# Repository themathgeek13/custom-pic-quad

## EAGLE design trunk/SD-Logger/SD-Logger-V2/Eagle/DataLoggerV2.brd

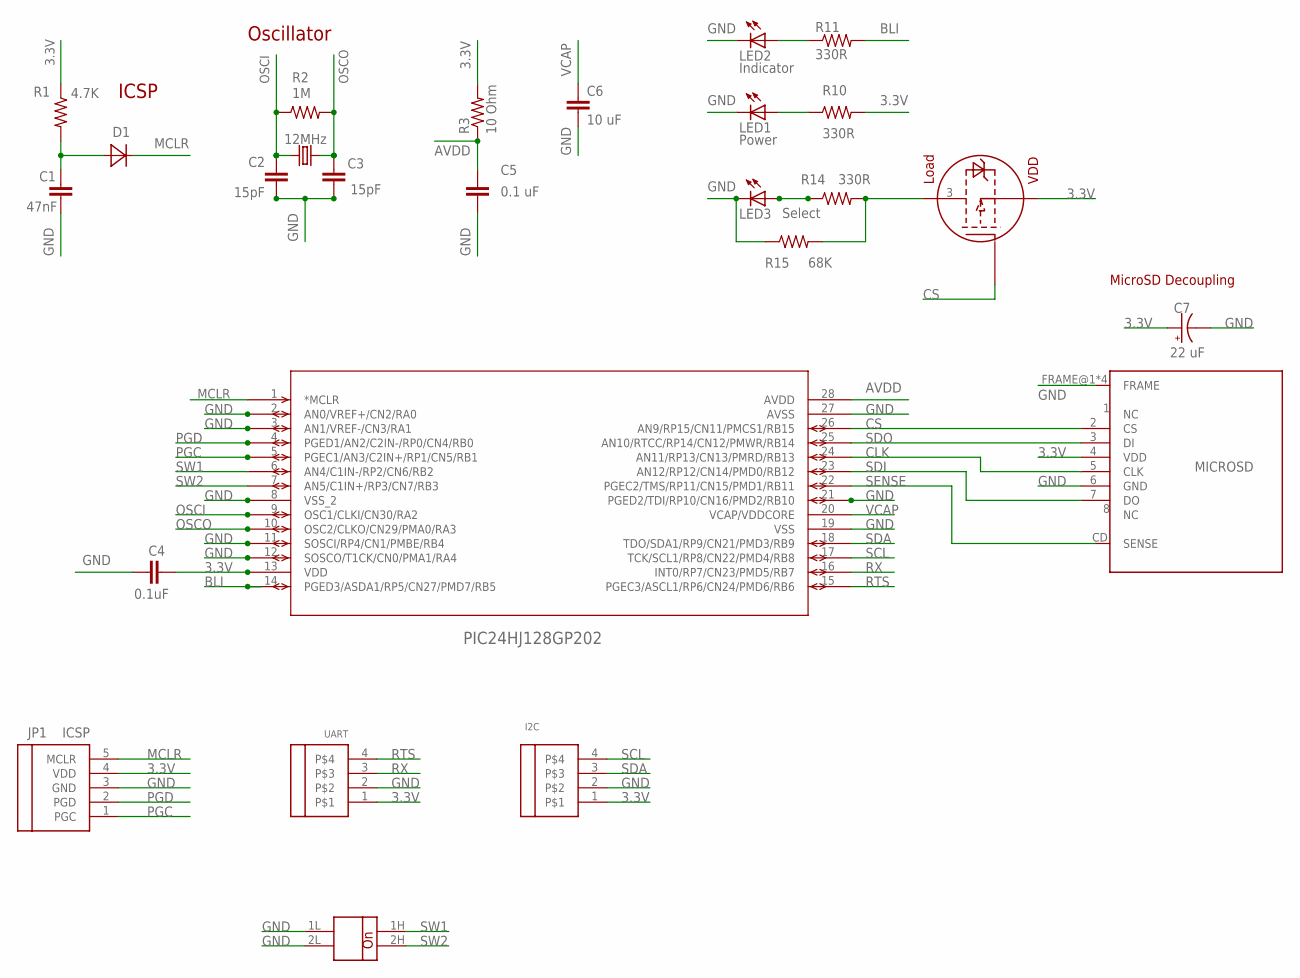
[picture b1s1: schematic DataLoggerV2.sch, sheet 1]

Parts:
C1: 47nF; 0805_INCH-HS-CAP
C2, C3: 15pF; 0805_INCH-HS-CAP
C4: 0.1uF; 0603_INCH-HS-CAP
C5: 0.1 uF; 0603_INCH-HS-CAP
C6: 10 uF; 1210_INCH-HS-CAP
C7: 22 uF; TANT-C-6032
D1: DIODE_1206; 1206_INCH-HS-DIODE
I2C: HEADER-04_JST-ZH_JST-ZH; 1X04-JST-ZH
JP1: ICSP; 1X05-JST-ZH
LED1: Power; 1206_INCH-HS-LED
LED2: Indicator; 1206_INCH-HS-LED
LED3: Select; 1206_INCH-HS-LED
P-FET: NTS2101P; SOT-323-0NSEMI
Q1: 12MHz; CRYSTAL-SMD-5.0X3.2
R1: 4.7K; 0805_INCH-HS
R2: 1M; 0805_INCH-HS
R3: 10 Ohm; 0805_INCH-HS
R10, R11, R14: 330R; 0805_INCH-HS
R15: 68K; 0805_INCH-HS
U$1: PIC24HJ128GP202; SOIC28-W_MC
U$2: MICROSD; MICROSD_V1
U$3: SWITCH-2_HALF-PITCH; DIP-2-HP
UART: HEADER-04_JST-ZH_JST-ZH; 1X04-JST-ZH

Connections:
3.3V: C4.1, C7.+, I2C.1, JP1.4 (VDD), P-FET.2 (S), R1.1, R3.2, R10.2, U$1.13 (VDD), U$2.4 (VDD), UART.1; also elsewhere on the board
AVDD: C5.1, R3.1, U$1.28 (AVDD)
BLI: R11.2, U$1.14 (PGED3/ASDA1/RP5/CN27/PMD7/RB5)
CLK: U$1.24 (AN11/RP13/CN13/PMRD/RB13), U$2.5 (CLK); also elsewhere on the board
CS: P-FET.1 (G), U$1.26 (AN9/RP15/CN11/PMCS1/RB15), U$2.2 (CS); also elsewhere on the board
GND: C1.2, C2.1, C3.1, C4.2, C5.2, C6.P$2 (2), C7.-, I2C.2, JP1.3 (GND), LED1.C, LED2.C, LED3.C, R15.1, U$1.2 (AN0/VREF+/CN2/RA0), U$1.3 (AN1/VREF-/CN3/RA1), U$1.8 (VSS_2), U$1.11 (SOSCI/RP4/CN1/PMBE/RB4), U$1.12 (SOSCO/T1CK/CN0/PMA1/RA4), U$1.19 (VSS), U$1.21 (PGED2/TDI/RP10/CN16/PMD2/RB10), U$1.27 (AVSS), U$2.6 (GND), U$2.FRAME@1 (FRAME), U$2.FRAME@2 (FRAME), U$2.FRAME@3 (FRAME), U$2.FRAME@4 (FRAME), U$3.1L, U$3.2L, UART.2; also elsewhere on the board
MCLR: D1.C, JP1.5 (MCLR), U$1.1 (*MCLR)
unnamed: C1.1, D1.A, R1.2
unnamed: LED3.A, R14.1
unnamed: LED1.A, R10.1
unnamed: LED2.A, R11.1
unnamed: P-FET.3 (D), R14.2, R15.2
OSCI: C2.2, Q1.P$2 (2), R2.1, U$1.9 (OSC1/CLKI/CN30/RA2)
OSCO: C3.2, Q1.P$1 (1), R2.2, U$1.10 (OSC2/CLKO/CN29/PMA0/RA3)
PGC: JP1.1 (PGC), U$1.5 (PGEC1/AN3/C2IN+/RP1/CN5/RB1)
PGD: JP1.2 (PGD), U$1.4 (PGED1/AN2/C2IN-/RP0/CN4/RB0)
RTS: U$1.15 (PGEC3/ASCL1/RP6/CN24/PMD6/RB6), UART.4; also elsewhere on the board
RX: U$1.16 (INT0/RP7/CN23/PMD5/RB7), UART.3; also elsewhere on the board
SCL: I2C.4, U$1.17 (TCK/SCL1/RP8/CN22/PMD4/RB8); also elsewhere on the board
SDA: I2C.3, U$1.18 (TDO/SDA1/RP9/CN21/PMD3/RB9); also elsewhere on the board
SDI: U$1.23 (AN12/RP12/CN14/PMD0/RB12), U$2.7 (DO); also elsewhere on the board
SDO: U$1.25 (AN10/RTCC/RP14/CN12/PMWR/RB14), U$2.3 (DI); also elsewhere on the board
SENSE: U$1.22 (PGEC2/TMS/RP11/CN15/PMD1/RB11), U$2.CD (SENSE)
SW1: U$1.6 (AN4/C1IN-/RP2/CN6/RB2), U$3.1H
SW2: U$1.7 (AN5/C1IN+/RP3/CN7/RB3), U$3.2H
VCAP: C6.P$1 (1), U$1.20 (VCAP/VDDCORE)

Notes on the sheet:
ICSP
Oscillator
MicroSD Decoupling

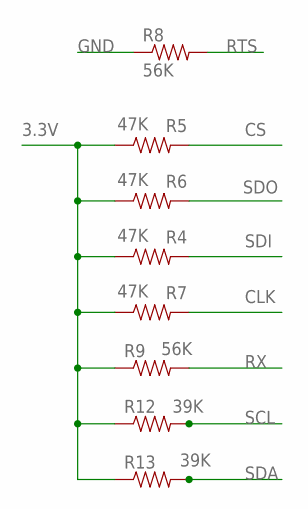
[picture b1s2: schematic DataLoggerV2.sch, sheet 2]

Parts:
R4, R5, R6, R7: 47K; 0805_INCH-HS
R8, R9: 56K; 0805_INCH-HS
R12, R13: 39K; 0805_INCH-HS

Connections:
3.3V: R4.1, R5.1, R6.1, R7.1, R9.1, R12.1, R13.1; also elsewhere on the board
CLK: R7.2; also elsewhere on the board
CS: R5.2; also elsewhere on the board
GND: R8.1; also elsewhere on the board
RTS: R8.2; also elsewhere on the board
RX: R9.2; also elsewhere on the board
SCL: R12.2; also elsewhere on the board
SDA: R13.2; also elsewhere on the board
SDI: R4.2; also elsewhere on the board
SDO: R6.2; also elsewhere on the board

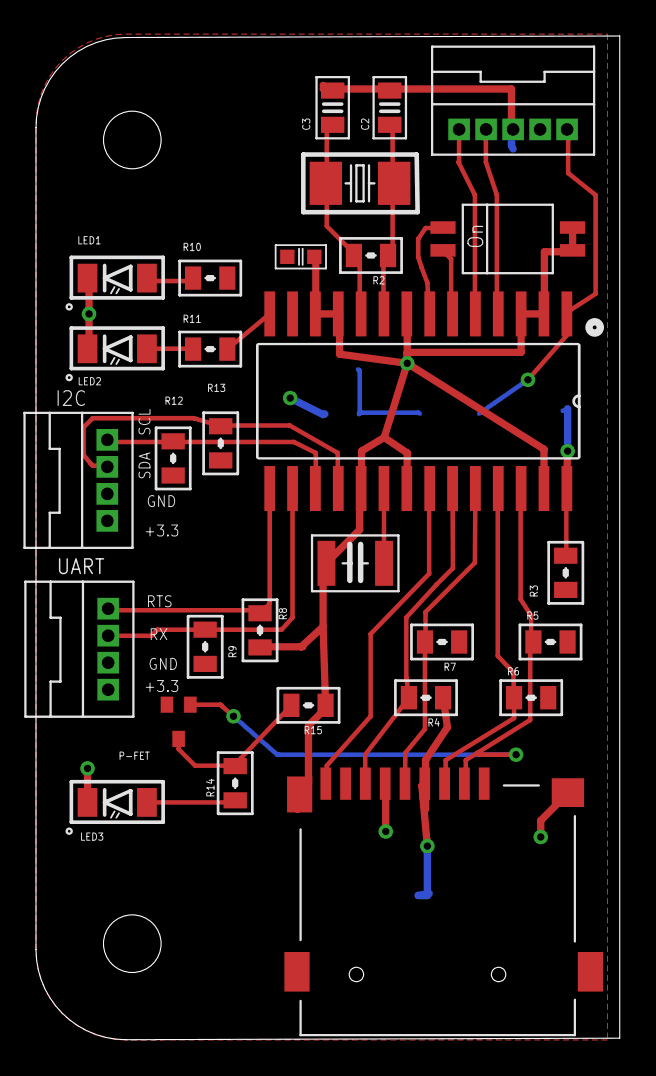
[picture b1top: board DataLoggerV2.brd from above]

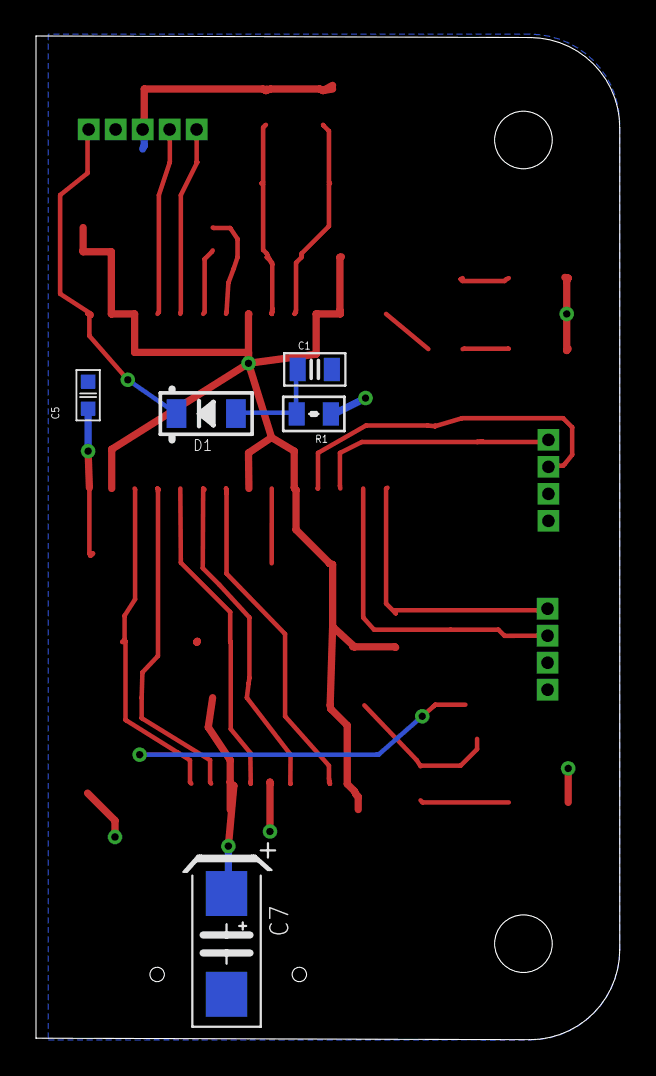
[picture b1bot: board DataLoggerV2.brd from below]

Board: 2 copper layers, 32.4 x 55.8 mm, 34 parts (5 on the bottom side), 26 nets.

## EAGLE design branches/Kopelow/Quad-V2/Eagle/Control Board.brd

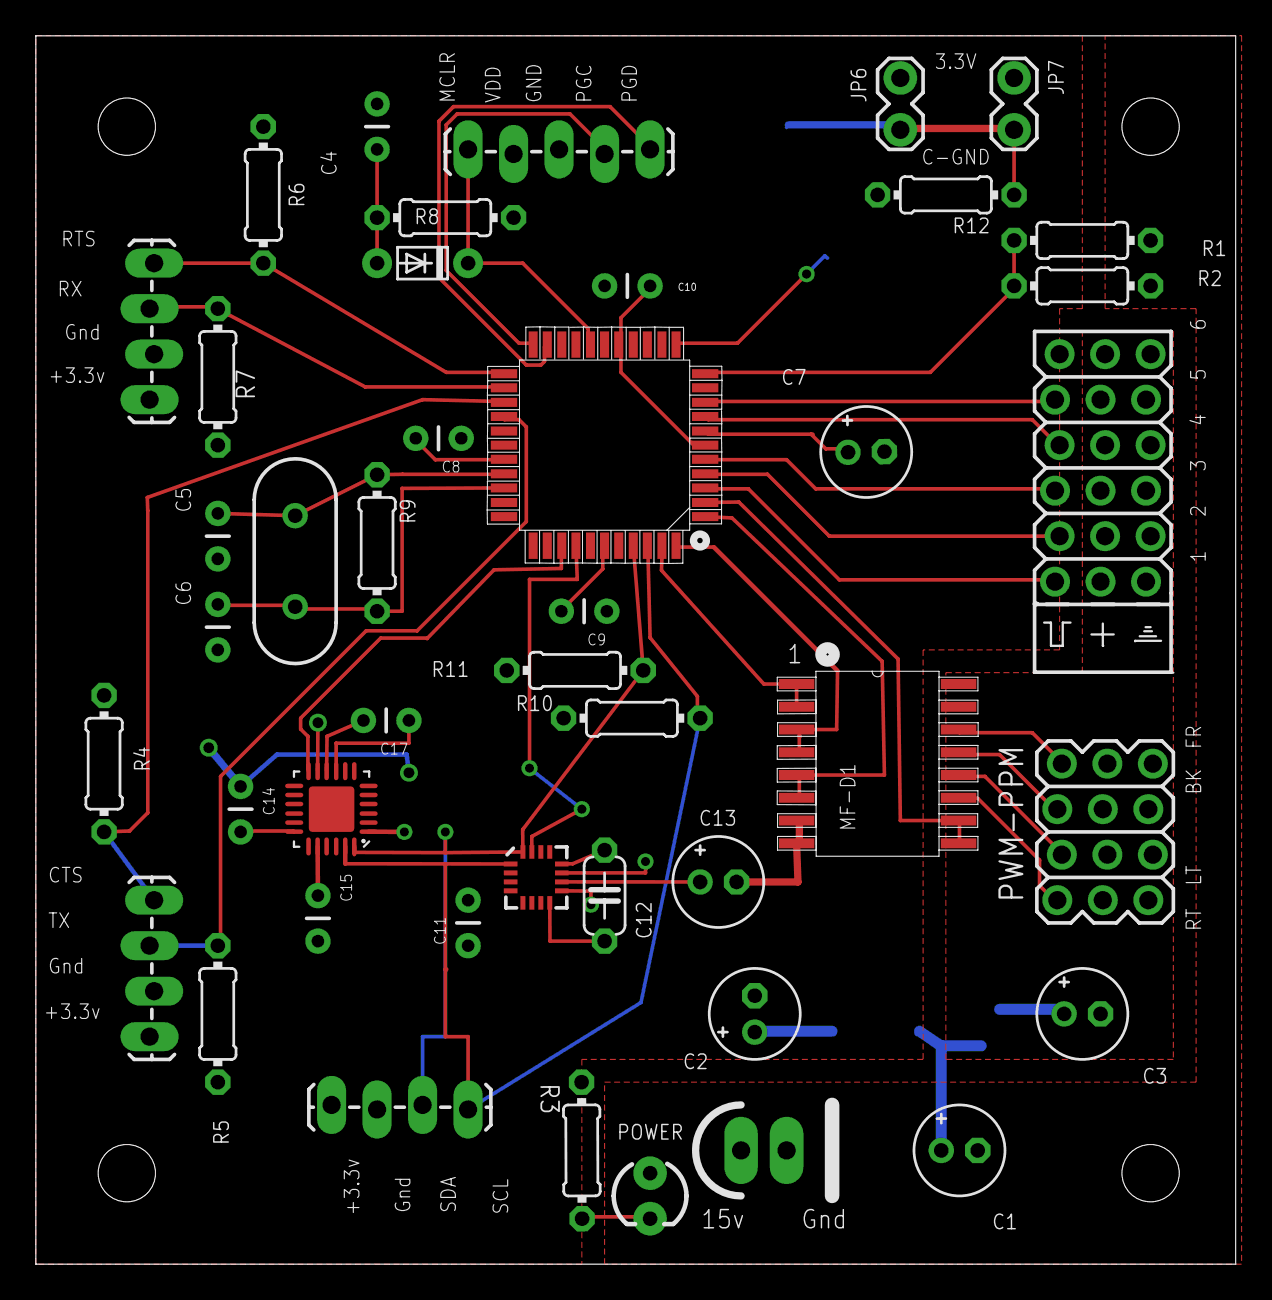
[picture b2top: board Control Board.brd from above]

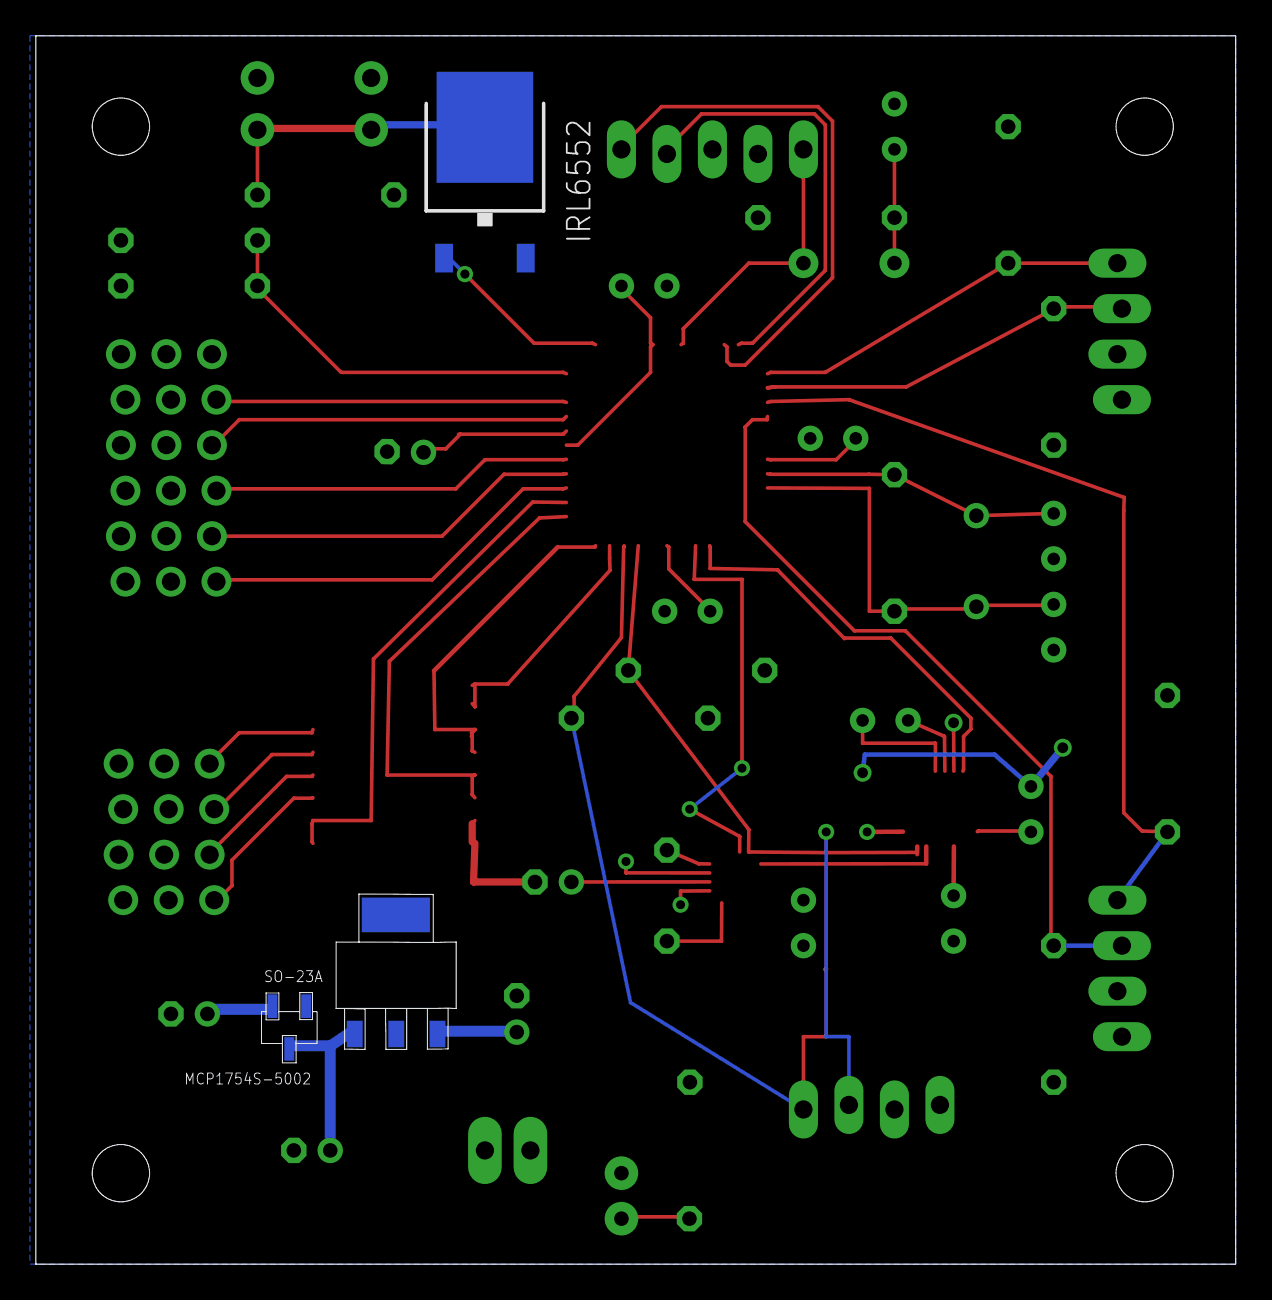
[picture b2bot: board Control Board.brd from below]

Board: 2 copper layers, 67.0 x 68.6 mm, 47 parts (3 on the bottom side), 41 nets.

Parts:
C1: 47uF; E2-5
C2, C3, C7: 10uF; E2-5
C4: 47nF; CAP-SMALL-2MM-SMALLPAD
C5, C6: 22pF; CAP-SMALL-2MM-SMALLPAD
C8, C9, C10, C11, C14, C17: 0.1uF; CAP-SMALL-2MM-SMALLPAD
C12: .22uF; C050-024X044
C13: 4.7uF; E2-5
C15: 2.2nF; CAP-SMALL-2MM-SMALLPAD
CR1: CORONA-6CH-RECEIVER; CORONA-6CH-RECEIVER-FOOTPRINT
D1: 1N914; DO34-5
IRL6552: IRLR6225_MOSFET; TO252
JP1: Battery; 1X02_LONGPADS
JP2: ICSP; ICSP_LOCK_LONGPADS
JP3: RX(In); 1X04_LOCK_LONGPADS
JP4: TX(Out); 1X04_LOCK_LONGPADS
JP5: I2C; 1X04_LOCK_LONGPADS
JP6, JP7: 1X02_LOCK
MCP1703X-3302: SOT-223-3; SOT-223_3MC
MCP1754S-5002: SO-23A; SOT-23A_MC
MF-D1: TC4469XOE; SOIC16_W_MC
POWER: LED3MM
PWM-PPM: 4CH-PWM-PPM-HEADER; 4CH-PWM-PPM-HEADER-PACKAGE
Q1: 12MHz; HC49US
R1: 8.2k; 0204/7
R2: 2.2k; 0204/7
R3, R8: 4.7K; 0204/7
R4, R5, R6, R7: 40k; 0204/7
R9: 1M; 0204/7
R10, R11: 3.3K; 0204/7
R12: 100K; 0204/7
U1: HMC5883LSMD; HMC5883L-16LPCC
U$1: MPU-6050-1; MPU-6050_QFN-24-4MM2_AZ
U$3: PIC24HJ128GP204_AZ; TQFP44_10X10MC

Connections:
3.3V: C2.+, C8.1, C9.1, C10.1, C11.2, C14.1, JP2.2, JP3.1, JP4.1, JP5.1, JP6.1, JP7.2, MCP1703X-3302.3, R5.2, R7.2, R8.1, R10.2, R11.2, R12.2, U1.2, U1.4, U1.13, U$1.8, U$1.13, U$3.17, U$3.28, U$3.40
5V: C3.+, CR1.P1, CR1.P2, CR1.P3, CR1.P4, CR1.P5, CR1.P6, MCP1754S-5002.2, MF-D1.15, MF-D1.16
15V: C1.+, JP1.2, MCP1703X-3302.1, MCP1754S-5002.3, POWER.A, R1.1
BCHK: R1.2, R2.1, U$3.11
BLI: IRL6552.1, U$3.12
C1: C13.+, U1.10
CH1: CR1.1, U$3.3
CH2: CR1.2, U$3.4
CH3: CR1.3, U$3.5
CH4: CR1.4, U$3.8
CH5: CR1.5, U$3.9
GND: C1.-, C2.-, C3.-, C4.2, C5.1, C6.1, C7.-, C8.2, C9.2, C10.2, C11.1, C13.-, C14.2, C15.2, C17.1, CR1.G1, CR1.G2, CR1.G3, CR1.G4, CR1.G5, CR1.G6, IRL6552.2, JP1.1, JP2.3, JP3.2, JP4.2, JP5.2, MCP1703X-3302.2, MCP1703X-3302.4, MCP1754S-5002.1, MF-D1.7, MF-D1.8, PWM-PPM.G1, PWM-PPM.G2, PWM-PPM.G3, PWM-PPM.G4, R2.2, R3.1, R4.2, R6.2, U1.9, U1.11, U$1.1, U$1.9, U$1.11, U$1.18, U$3.6, U$3.16, U$3.29, U$3.39
INT-AG: U$1.12, U$3.36
INT-M: U1.15, U$3.37
MCLR: D1.C, JP2.1, U$3.18
unnamed: C4.1, D1.A, R8.2
unnamed: IRL6552.3, JP6.2, JP7.1, R12.1
unnamed: C17.2, U$1.10
unnamed: POWER.K, R3.2
unnamed: C15.1, U$1.20
OC1: MF-D1.1, MF-D1.2, U$3.43
OC2: MF-D1.3, MF-D1.4, U$3.44
OC3: MF-D1.5, MF-D1.6, U$3.1
OC4: MF-D1.9, MF-D1.10, U$3.2
OSCI: C5.2, Q1.2, R9.1, U$3.30
OSCO: C6.2, Q1.1, R9.2, U$3.31
PGC: JP2.4, U$3.22
PGD: JP2.5, U$3.21
PWM1: MF-D1.14, PWM-PPM.1
PWM2: MF-D1.13, PWM-PPM.2
PWM3: MF-D1.12, PWM-PPM.3
PWM4: MF-D1.11, PWM-PPM.4
SCL: JP5.4, R10.1, U1.1, U$1.23, U$3.42
SDA: JP5.3, R11.1, U1.16, U$1.24, U$3.41
SETC: C12.2, U1.12
SETP: C12.1, U1.8
U1CTS: JP4.4, R4.1, U$3.25
U1RTS: JP3.4, R6.1, U$3.23
U1RX: JP3.3, R7.1, U$3.24
U1TX: JP4.3, R5.1, U$3.26
VCAP: C7.+, U$3.7

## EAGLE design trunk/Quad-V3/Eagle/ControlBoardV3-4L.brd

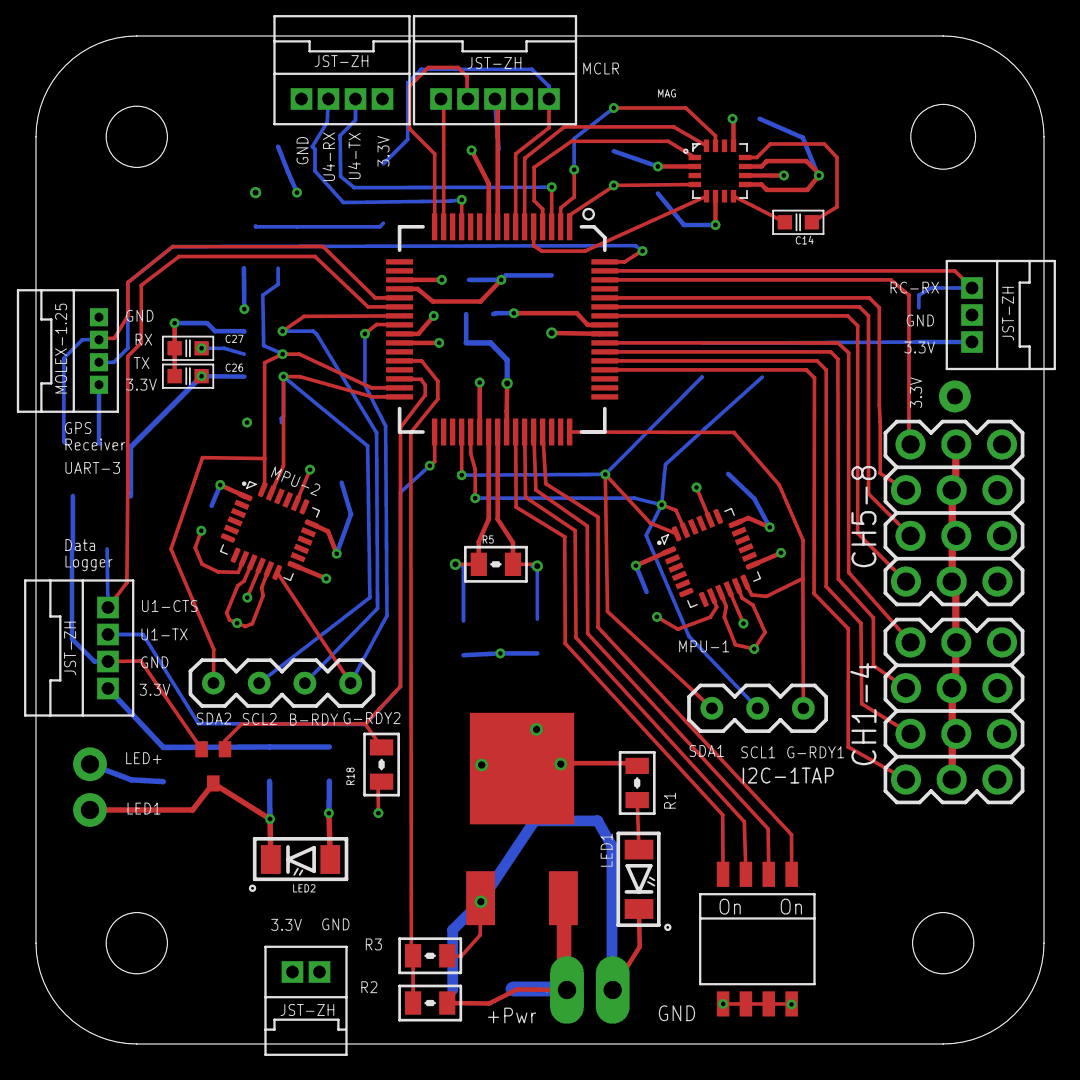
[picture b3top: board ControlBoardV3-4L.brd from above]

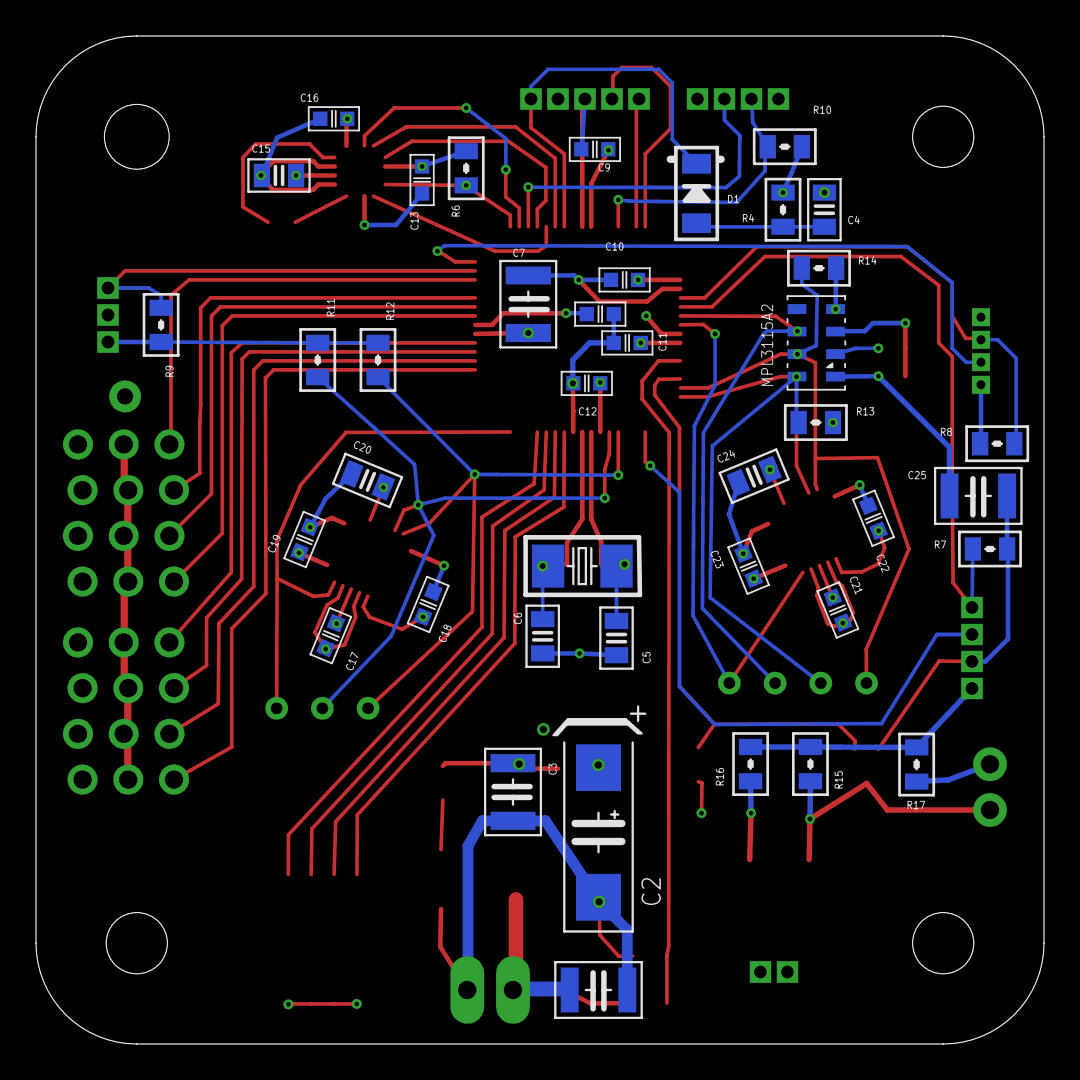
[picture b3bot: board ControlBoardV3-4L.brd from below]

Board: 4 copper layers, 56.0 x 56.0 mm, 70 parts (40 on the bottom side), 56 nets.

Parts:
C1, C3: 100 uF; 1210_INCH-HS-CAP
C2: 470 uF; TANT-D-7343
C4: 47nF; 0805_INCH-HS-CAP
C5, C6: 15pF; 0805_INCH-HS-CAP
C7, C25: 10uF; 1210_INCH-HS-CAP
C8: 0.1uF / 57; 0603_INCH-HS-CAP
C9: 0.1uF / 10; 0603_INCH-HS-CAP
C10: 0.1uF/19; 0603_INCH-HS-CAP
C11: 0.1uF/26; 0603_INCH-HS-CAP
C12: 0.1uF/38; 0603_INCH-HS-CAP
C13, C16, C17, C19, C21, C23, C26, C27: 0.1uF; 0603_INCH-HS-CAP
C14: 0.22uF; 0603_INCH-HS-CAP
C15: 4.7uF; 0805_INCH-HS-CAP
C18, C22: 10nF; 0603_INCH-HS-CAP
C20, C24: 2.2nF; 0805_INCH-HS-CAP
CH1-4, CH5-8: 4CH-PWM-PPM-HEADER-PACKAGE
D1: DIODE_1206; 1206_INCH-HS-DIODE
I2C-1TAP: HEADER-03_MACHINED; 1X03-100MIL-MACHINED
ICSP: JST-ZH; 1X05-JST-ZH
JP1: 1X02-JST-ZH
JP2: 1X02_100MIL_NO_SILK
LED1: Power; 1206_INCH-HS-LED
LED2: 1206_INCH-HS-LED
MAG: HMC5983L; HMC5X83L-16LPCC
MPL3115A2: MPL-3115A2
MPU-1, MPU-2: MPU-6050_QFN-24-4MM2_AZ
POWER: 12V; 1X02_100MIL_LONGPADS
Q1: 12MHz; CRYSTAL-SMD-5.0X3.2
R1, R3, R16: 1K; 0805_INCH-HS
R2: 3.3K; 0805_INCH-HS
R4: 4.7K; 0805_INCH-HS
R5: 1M; 0805_INCH-HS
R6, R7, R8, R9, R10: 47K; 0805_INCH-HS
R11, R12, R13, R14: 1.5K; 0805_INCH-HS
R15: 39K; 0805_INCH-HS
R17: 470R; 0805_INCH-HS
R18: 68K; 0805_INCH-HS
U$1: PIC24EP512GP806_TQFP64-10X10; TQFP64-10X10X1MM
U$2: NCP1117_DPAK; DPAK-ONSEMI
U$3: SWITCH-4_HALF-PITCH; DIP-4-HP
U$4: I2C-2 Tap; 1X04-100MIL-MACHINED
U$5: N-MOSFET_SOT-323; SOT-323
U$6: TAP-01_PRECISE; 1X01_PRECISE
UART-1: Data Logger; 1X04-JST-ZH
UART-2: RC Receiver; 1X03-JST-ZH
UART-3: GPS Receiver; 1X04-MOLEX-PICOBLADE
UART-4: US-100 Receiver; 1X04-JST-ZH

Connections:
+12V: C1.P$1, POWER.1, R2.1, U$2.3
B-RDY: MPL3115A2.INT1, U$1.23, U$4.2
BAT: R2.2, R3.1, U$1.28
BLI: R18.2, U$1.30, U$5.1
C-RESRV: C15.1, MAG.10
CAP: C27.1, MPL3115A2.CAP
CH1: CH1-4.4, U$1.52
CH2: CH1-4.3, U$1.53
CH3: CH1-4.2, U$1.54
CH4: CH1-4.1, U$1.55
CH5: CH5-8.4, U$1.58
CH6: CH5-8.3, U$1.59
CH7: CH5-8.2, U$1.60
CH8: CH5-8.1, U$1.62
CS: MAG.4, R6.1, U$1.1
CTS-U1: R7.2, U$1.22, UART-1.4
ESC-PWR: CH1-4.P1, CH1-4.P2, CH1-4.P3, CH1-4.P4, CH5-8.P1, CH5-8.P2, CH5-8.P3, CH5-8.P4
G-RDY1: I2C-1TAP.1, MPU-1.12, U$1.48
G-RDY2: MPU-2.12, U$1.24, U$4.1
GND: C1.P$2, C2.-, C3.P$2, C4.2, C5.1, C6.1, C7.P$2, C8.2, C9.2, C10.2, C11.2, C12.2, C13.2, C15.2, C16.2, C17.2, C18.1, C19.1, C20.2, C21.2, C22.1, C23.1, C24.2, C25.P$2, C26.2, C27.2, CH1-4.G1, CH1-4.G2, CH1-4.G3, CH1-4.G4, CH5-8.G1, CH5-8.G2, CH5-8.G3, CH5-8.G4, ICSP.3, JP1.1, LED1.C, MAG.6, MAG.9, MAG.11, MPL3115A2.GND, MPU-1.1, MPU-1.9, MPU-1.11, MPU-1.18, MPU-2.1, MPU-2.9, MPU-2.11, MPU-2.18, POWER.2, R3.2, R7.1, R18.1, U$1.9, U$1.20, U$1.25, U$1.41, U$2.1, U$3.1L, U$3.2L, U$3.3L, U$3.4L, U$5.2, UART-1.2, UART-2.2, UART-3.4, UART-4.1
M-RDY: MAG.15, U$1.2
M-SDI: MAG.5, U$1.5
M-SDO: MAG.16, U$1.6
MCLR: D1.C, ICSP.5, U$1.7
unnamed: LED1.A, R1.2
unnamed: C21.1, MPU-2.10
unnamed: C24.1, MPU-2.20
unnamed: C17.1, MPU-1.10
unnamed: JP2.2, R17.1
unnamed: JP2.1, LED2.C, R15.1, U$5.3
unnamed: LED2.A, R16.1
unnamed: C4.1, D1.A, R4.2
unnamed: C20.1, MPU-1.20
OSC1: C5.2, Q1.P$2, R5.1, U$1.39
OSC2: C6.2, Q1.P$1, R5.2, U$1.40
PGC: ICSP.1, U$1.15
PGD: ICSP.2, U$1.16
RX-U2: R9.2, U$1.63, UART-2.1
RX-U3: R8.2, U$1.21, UART-3.3
RX-U4: R10.2, U$1.13, UART-4.2
SCK: MAG.1, U$1.4
SCL1: I2C-1TAP.2, MPU-1.23, R11.2, U$1.37
SCL2: MPL3115A2.SCL, MPU-2.23, R13.2, U$1.32, U$4.3
SDA1: I2C-1TAP.3, MPU-1.24, R12.2, U$1.36
SDA2: MPL3115A2.SDA, MPU-2.24, R14.2, U$1.31, U$4.4
SETC: C14.1, MAG.12
SETP: C14.2, MAG.8
SW1: U$1.42, U$3.1H
SW2: U$1.43, U$3.2H
SW3: U$1.44, U$3.3H
SW4: U$1.45, U$3.4H
TX-U1: U$1.33, UART-1.3
TX-U3: U$1.64, UART-3.2
TX-U4: U$1.3, UART-4.3
VCAP: C7.P$1, U$1.56
VDD: C2.+, C3.P$1, C8.1, C9.1, C10.1, C11.1, C12.1, C13.1, C16.1, C18.2, C19.2, C22.2, C23.2, C25.P$1, C26.1, ICSP.4, JP1.2, MAG.2, MAG.13, MPL3115A2.VDD, MPL3115A2.VIO, MPU-1.8, MPU-1.13, MPU-2.8, MPU-2.13, R1.1, R4.1, R6.2, R8.1, R9.1, R10.1, R11.1, R12.1, R13.1, R14.1, R15.2, R16.2, R17.2, U$1.10, U$1.19, U$1.26, U$1.38, U$1.57, U$2.2, U$6.1, UART-1.1, UART-2.3, UART-3.1, UART-4.4

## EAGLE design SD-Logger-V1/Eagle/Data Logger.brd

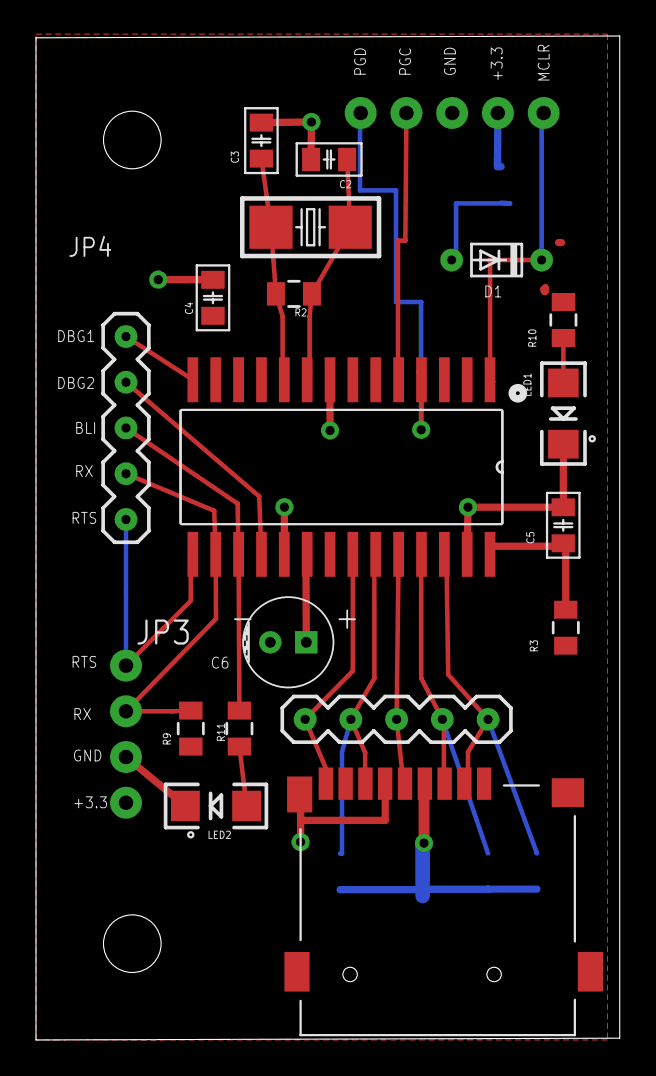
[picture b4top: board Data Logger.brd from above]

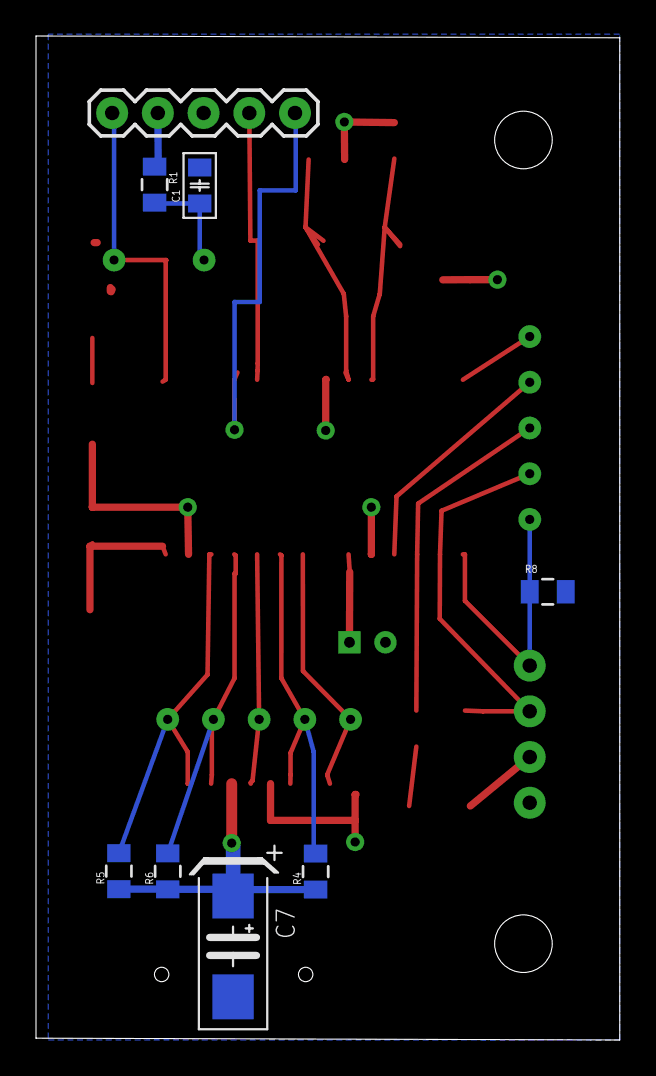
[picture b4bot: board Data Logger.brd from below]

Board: 2 copper layers, 32.4 x 55.8 mm, 27 parts (8 on the bottom side), 22 nets.

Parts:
C1: 47nF; 0805_INCH-HS-CAP
C2, C3: 22pF; 0805_INCH-HS-CAP
C4: 0.1uF; 0805_INCH-HS-CAP
C5: 0.1 uF; 0805_INCH-HS-CAP
C6: 10uF; CAP-ELE-5MM
C7: 22 uF; TANT-C-6032
D1: DIODE_TTH; DO34-5
JP1: ICSP; 1X05-PRECISE
JP2: HEADER-05_MACHINED; 1X05_MACHINED
JP3: HEADER-04_PRECISE-NO-SILK; 1X04-PRECISE-NO-SILK
JP4: DEBUG; 1X05_MACHINED
LED1: Green; 1206_INCH-HS-LED
LED2: Orange; 1206_INCH-HS-LED
Q1: 12MHz; CRYSTAL-SMD-5.0X3.2
R1: 4.7K; 0805_INCH-HS
R2: 1M; 0805_INCH-HS
R3: 10 Ohm; 0805_INCH-HS
R4, R5, R6: 47K; 0805_INCH-HS
R8, R9: 40K; 0805_INCH-HS
R10: 150; 0805_INCH-HS
R11: 330; 0805_INCH-HS
U$1: PIC24HJ128GP202; SOIC28-W_MC
U$2: MICROSD; MICROSD_V1

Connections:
3.3V: C4.1, C7.+, JP1.2, JP3.4, R1.1, R3.2, R4.1, R5.1, R6.1, R9.1, R10.2, U$1.13, U$2.4
BLI: JP4.3, R11.2, U$1.17
CLK: JP2.3, U$1.24, U$2.5
CS: JP2.1, R5.2, U$1.26, U$2.2
DBG1: JP4.5, U$1.14
DBG2: JP4.4, U$1.18
GND: C1.2, C2.1, C3.1, C4.2, C5.2, C6.-, C7.-, JP1.3, JP3.3, LED1.C, LED2.C, R8.1, U$1.8, U$1.19, U$1.27, U$2.6, U$2.FRAME@1, U$2.FRAME@2, U$2.FRAME@3, U$2.FRAME@4
MCLR: D1.C, JP1.1, U$1.1
unnamed: C1.1, D1.A, R1.2
unnamed: C5.1, R3.1, U$1.28
unnamed: LED1.A, R10.1
unnamed: LED2.A, R11.1
OSCI: C2.2, Q1.P$2, R2.1, U$1.9
OSCO: C3.2, Q1.P$1, R2.2, U$1.10
PGC: JP1.4, U$1.5
PGD: JP1.5, U$1.4
RTS: JP3.1, JP4.1, R8.2, U$1.15
RX: JP3.2, JP4.2, R9.2, U$1.16
SDI: JP2.4, R4.2, U$1.23, U$2.7
SDO: JP2.2, R6.2, U$1.25, U$2.3
SENSE: JP2.5, U$1.22, U$2.CD
VCAP: C6.+, U$1.20

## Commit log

2013-08-23 Initial directory structure.
2013-08-25 Notes: * What if we switch from dPV/dT to dE/dT (from process state derivative to error derivative)? * Looks like on "long turns" on Z-axis the "slow drift compensation" for Gz actually is negative a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
2013-08-25 Removing Source Control from the MPLab project in favor of using TortoiseSVN as MPLab IDE does not correctly sync shared files.
2013-08-27 This Tag identifies a working copy of the project (quad flies) with the derivative component calculated based upon the derivative of the ERROR of the controlled parameter.
2013-08-27 Working copy of the FW with the derivative components of PID are calculated based upon derivative of the controlled state variable (not the derivative of the ERROR as in a traditional PID)!
2013-08-31 Minor configuration changes
2013-09-28 This is the working copy of the code which calculates derivatives as dV/dT
2013-09-28 Code base using Gyro rates to calculate PID differential term
2013-09-28 Minor efficiency update - IMUInit stops magnetometer after calculating base Azimuth
2013-10-01 This is the version of RC module to work with 72 MHz receiver. The difference between this one and the 2.4 GHz version in the working copy is in the receiver pin-out.
2013-10-05 Restored (after crash!) version of Firmware that uses dP/dT to calculate state derivatives for PID; includes changes required to use the 2.4 GHz receiver (instead of the original 72Mhz one.
2013-10-05 Verified after crash
2013-10-16 Intermediate update - added module (MXB) to work with MaxBotix sonar, changed throttle logic to take into account battery discharge during flight, working on Matrix3D module to consolidate matrix ope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
2013-10-16 UART module updated to use Profile header to consolidate changes required when the pin assignment changes.
2013-10-17 Intermediate update - added project "12-Matrix3D" to test matrix operations; updated calculation of Angular Velocity (just to show the data for now) to use partial (no Yaw) DCM; updated DCM, IMU, and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
2013-10-31 Updated TMR routines to provide new functions to set and check for Alarms; increased resolution of real time calculation from 1 msec to 125 usec - now Delay and Alarm functions more precise. Added Ea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
2013-11-03 Release 1.1. Added functionality to fly in "+" and "X" configurations, added option for "Course Lock" a-la DJI Phantom, increased precision of TMRDelay function and added TMRSetAlarm and TMRWaitAlarm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
2013-11-03 Removed branch that worked with 72 MHz receiver - not practical anymore :)
2013-11-05 Added Eagle files
2013-11-26 Adding MPL3115 Barometric Sensor
2013-11-26 Just renaming some directories
2013-11-26 Finalizing rename of directories by renaming projects
2013-11-28 Removed MaxBotix from the project - data is very unstable; added MPL3115A2 Barometric Altimeter by Freescale. Modified HMCMAG to use Input Capture (IC2) module instead of INT2 and added HW Profile to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
2014-05-19 A fully functional Quad control firmware with MPL3115A barometric altimeter and US-20 ultrasonic sensor. Unfortunately precision is not sufficient for automatic landing without proper fusion of all a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
2014-05-19 Intermediate check-in in preparation for renaming some projects
2014-05-19 Split project "90-QCM" into two: "90-QCM_BasicControl" and "91-QCM_Altimetry". The former is the firmware that implements all quad control functions; the latter - augments the former with MPL3115A an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
2014-06-29 Prior to major rework of I2C module to allow for up to 2 buses
2014-07-06 Reworked I2C and MPU APIs
2014-07-06 Renaming some folders
2014-07-06 Added MPL and MPU Asynchronous access projects
2014-07-06 Renaming projects in the renamed directories
2014-07-06 Checkpoint prior to another review of I2C subscription model
2014-07-08 Adding missing file RCSym_Local.h
2014-07-13 I2C Library updated to provide to provide fully asynchronous operation with multiple subscribers.
2014-07-13 Some renaming in Quad-V2 subtree
2014-07-21 Added Eagle folder
2014-07-22 Reconfiguring projects after renaming directories
2014-07-24 Minor TMR cleanup
2014-07-30 Created wiki page through web user interface.
2014-07-31 Increased RC roll/pitch input to +/-35 degree; reduced level of IIR smoothing of RC input to IIR(2).
2014-08-12 Cosmetic HMCSPI changes
2014-08-22 Refactoring some of the V2 projects
2014-08-22 Testing SVN
2014-08-22 Create working branch for V2 controller - Rich Kopelow
2014-08-22 Create working directory for Rich Kopelow
2014-08-22 Initial load of base code with "mechanical" changes: Change directory path ‘/‘ to ‘\' (add MAC Compatibility) Change MPUSample => MPUData Change MPLSample => MPLData Replace UART. files to UART_TX. f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
2014-08-22 remove unused directory
2014-08-22 Ignore production Magnetometer library change in 42-MAG_Calibration
2014-08-22 cleanups
2014-08-22 Project interrupt handling source files changed and tested.
2014-08-23 Change project configuration to use current MAG code.
2014-08-23 Update Ignores
2014-08-23 Clean projects
2016-03-18 Migrating wiki contents from Google Code
